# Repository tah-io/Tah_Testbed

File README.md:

Tah_Testbed
===========

Contains all the python and arduino test sketches for Tah Testbed

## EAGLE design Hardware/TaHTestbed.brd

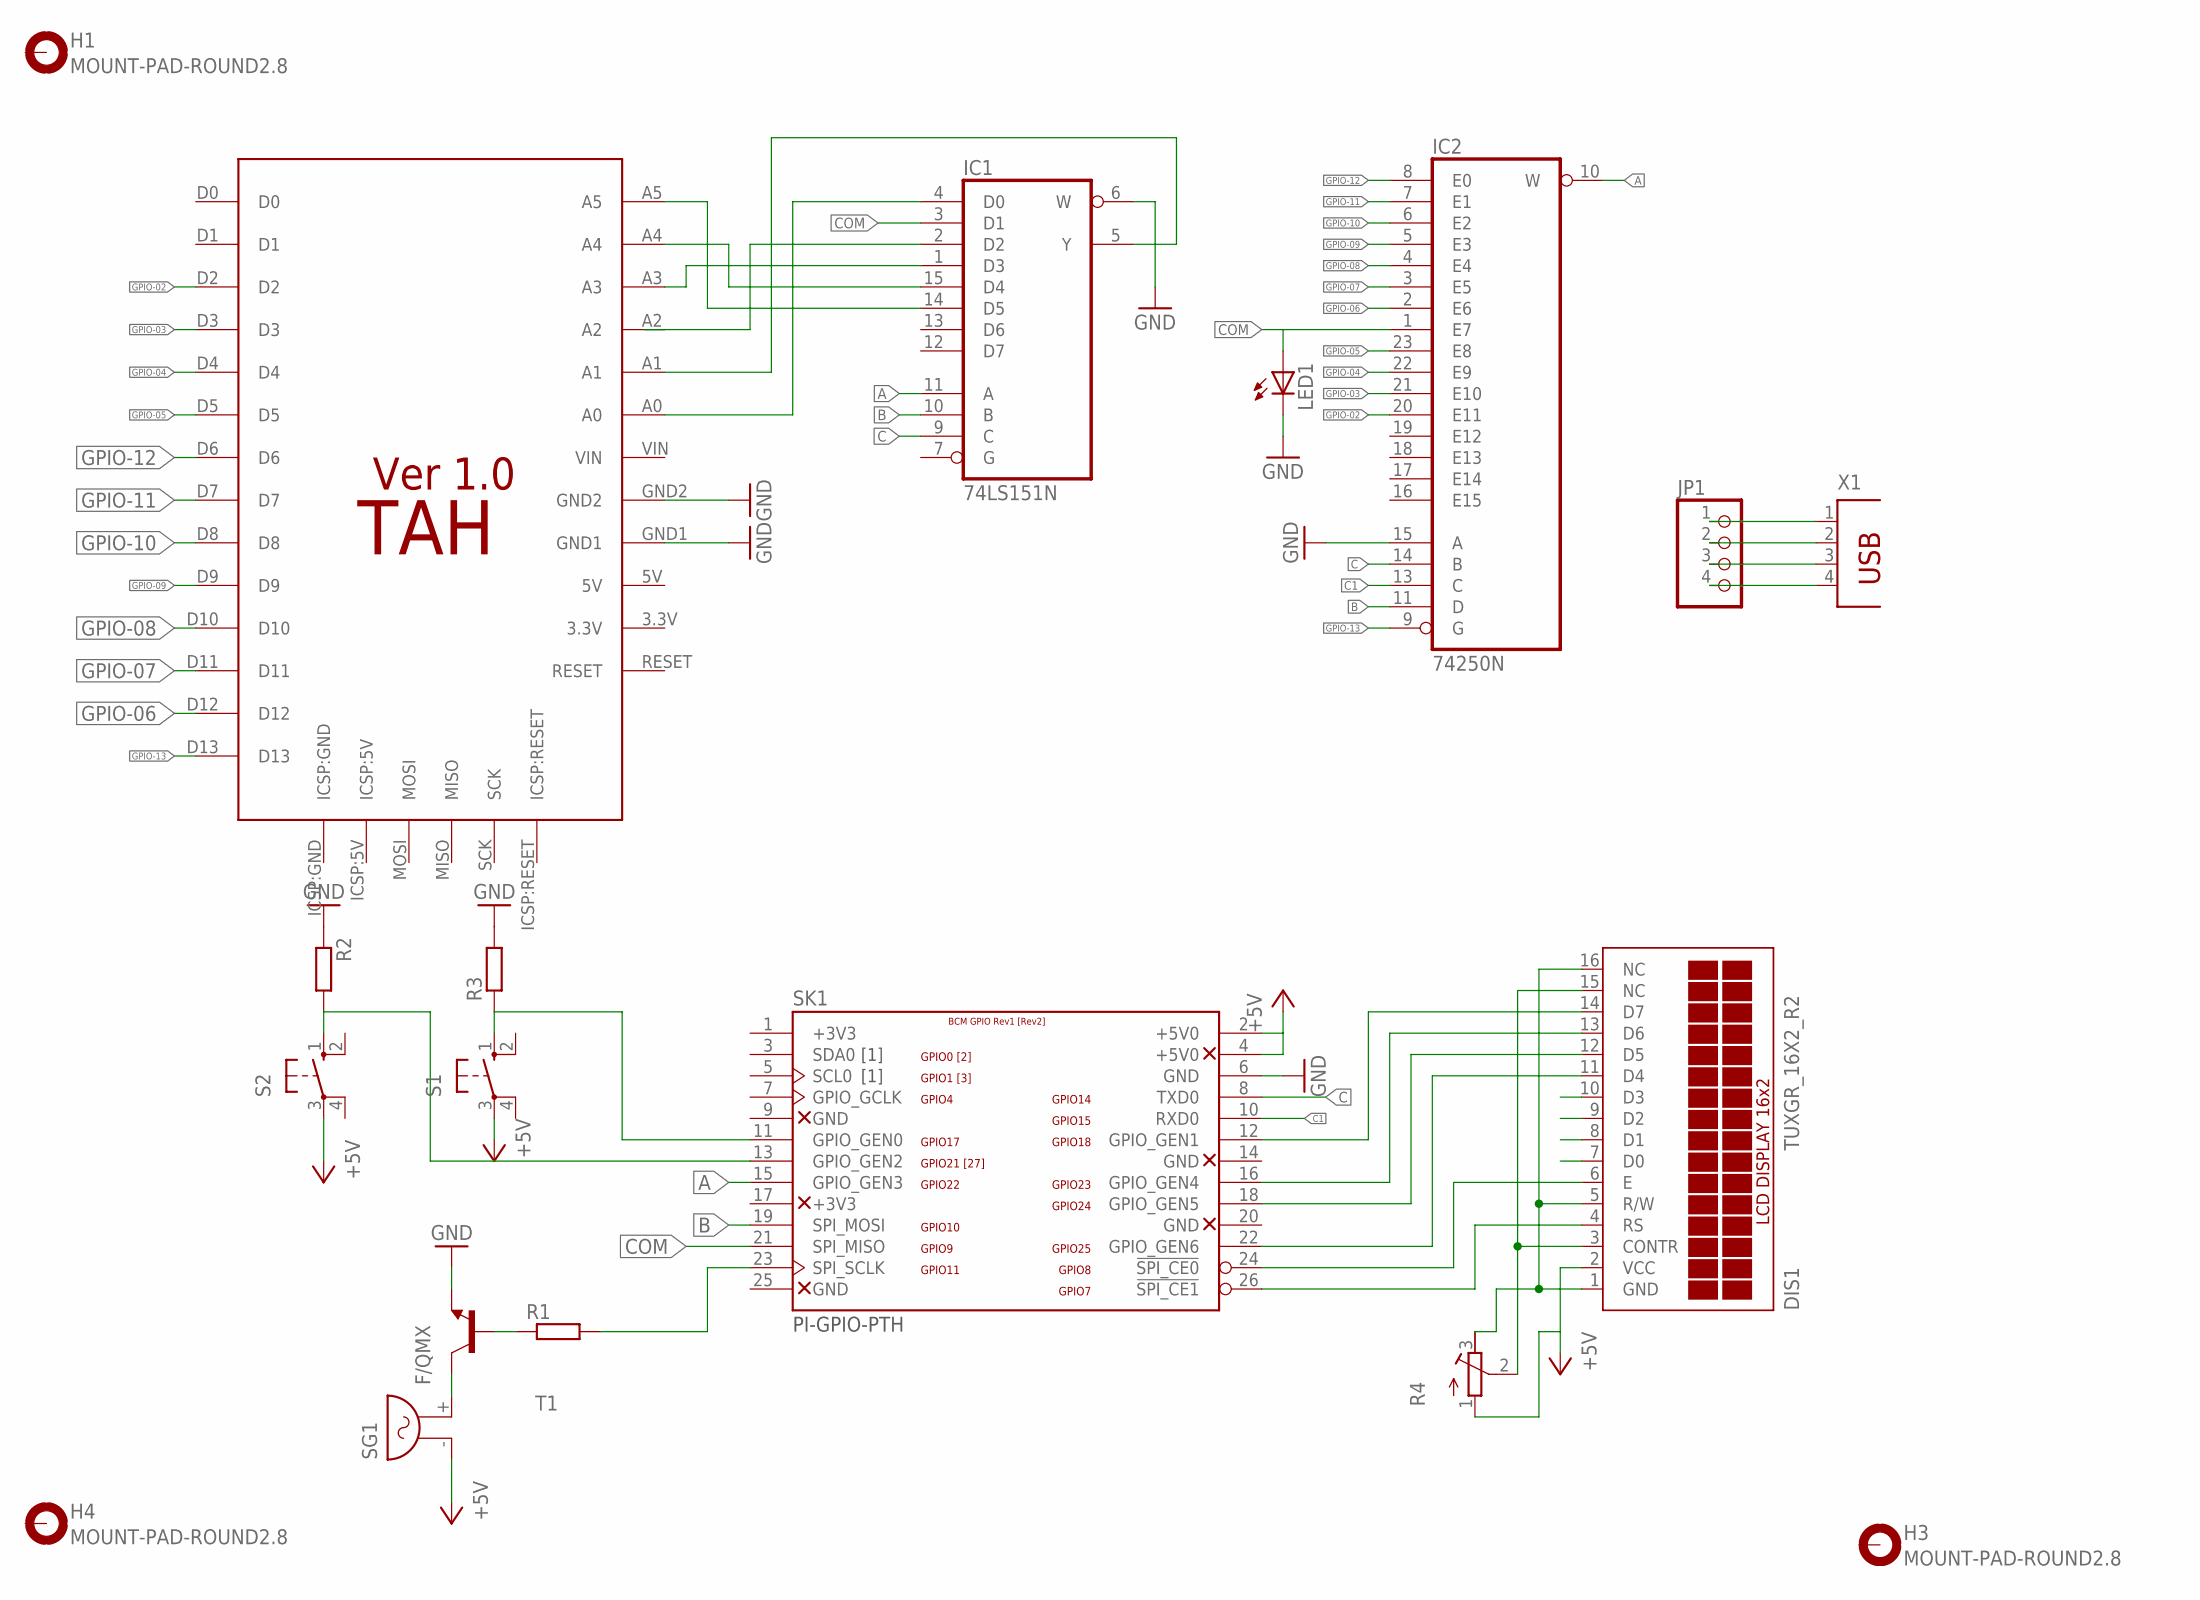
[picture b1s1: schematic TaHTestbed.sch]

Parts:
DIS1: TUXGR_16X2_R2
H1, H3, H4: MOUNT-PAD-ROUND2.8; 2,8-PAD
IC1: 74LS151N; DIL16
IC2: 74250N; DIL24-6
JP1: PINHD-1X4; 1X04
LED1: LEDCHIPLED_1206; CHIPLED_1206
R1: R-EU_0207/10; 0207/10
R2, R3: R-EU_0613/5V; P0613V
R4: R-TRIMM64Z; RTRIM64Z
S1, S2: 10-XX; B3F-10XX
SG1: F/QMX
SK1: PI-GPIO-PTH; GPIO-CONNECTOR
T1: BC547-NPN-TO92-CBE; TO92-CBE
U$2: TAH_FOOTPRINT_VER1.0; TAH_FOOTPRINT
X1: PN87520

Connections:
+3V3: SK1.1 (+3V3)
+5V: DIS1.2 (VCC), R4.1 (A), S1.3, S2.3, SG1.- (1), SK1.2 (+5V0), SK1.4 (+5V0)
A: IC1.11 (A), IC2.10 (W), SK1.15 (GPIO_GEN3)
B: IC1.10 (B), IC2.11 (D), SK1.19 (SPI_MOSI)
C: IC1.9 (C), IC2.14 (B), SK1.8 (TXD0)
C1: IC2.13 (C), SK1.10 (RXD0)
CM_IN: IC1.4 (D0), U$2.A0
COM: IC1.3 (D1), IC2.1 (E7), LED1.A, SK1.21 (SPI_MISO)
GND: IC1.6 (W), IC1.8 (GND), IC2.12 (GND), IC2.15 (A), LED1.C, R2.1, R3.2, SK1.6 (GND), T1.E, U$2.GND1, U$2.GND2
GPIO-02: IC2.20 (E11), U$2.D2
GPIO-03: IC2.21 (E10), U$2.D3
GPIO-04: IC2.22 (E9), U$2.D4
GPIO-05: IC2.23 (E8), U$2.D5
GPIO-06: IC2.2 (E6), U$2.D12
GPIO-07: IC2.3 (E5), U$2.D11
GPIO-08: IC2.4 (E4), U$2.D10
GPIO-09: IC2.5 (E3), U$2.D9
GPIO-10: IC2.6 (E2), U$2.D8
GPIO-11: IC2.7 (E1), U$2.D7
GPIO-12: IC2.8 (E0), U$2.D6
GPIO-13: IC2.9 (G), U$2.D13
unnamed: IC1.14 (D5), U$2.A5
unnamed: IC1.15 (D4), U$2.A4
unnamed: IC1.1 (D3), U$2.A3
unnamed: DIS1.4 (RS), SK1.26 (!SPI_CE1)
unnamed: IC1.2 (D2), U$2.A2
unnamed: DIS1.6 (E), SK1.24 (!SPI_CE0)
unnamed: DIS1.11 (D4), SK1.22 (GPIO_GEN6)
unnamed: DIS1.12 (D5), SK1.18 (GPIO_GEN5)
unnamed: DIS1.13 (D6), SK1.16 (GPIO_GEN4)
unnamed: DIS1.14 (D7), SK1.12 (GPIO_GEN1)
unnamed: JP1.1, X1.1
unnamed: IC1.5 (Y), U$2.A1
unnamed: DIS1.1 (GND), DIS1.5 (R/W), DIS1.16 (NC), R4.3 (E)
unnamed: R1.2, SK1.23 (SPI_SCLK)
unnamed: R1.1, T1.B
unnamed: DIS1.3 (CONTR), DIS1.15 (NC), R4.2 (S)
unnamed: SG1.+ (2), T1.C
unnamed: R3.1, S1.1 (S), SK1.11 (GPIO_GEN0)
unnamed: R2.2, S2.1 (S), SK1.13 (GPIO_GEN2)
unnamed: JP1.2, X1.2
unnamed: JP1.3, X1.3
unnamed: JP1.4, X1.4
VCC: IC1.16 (VCC), IC2.24 (VCC)

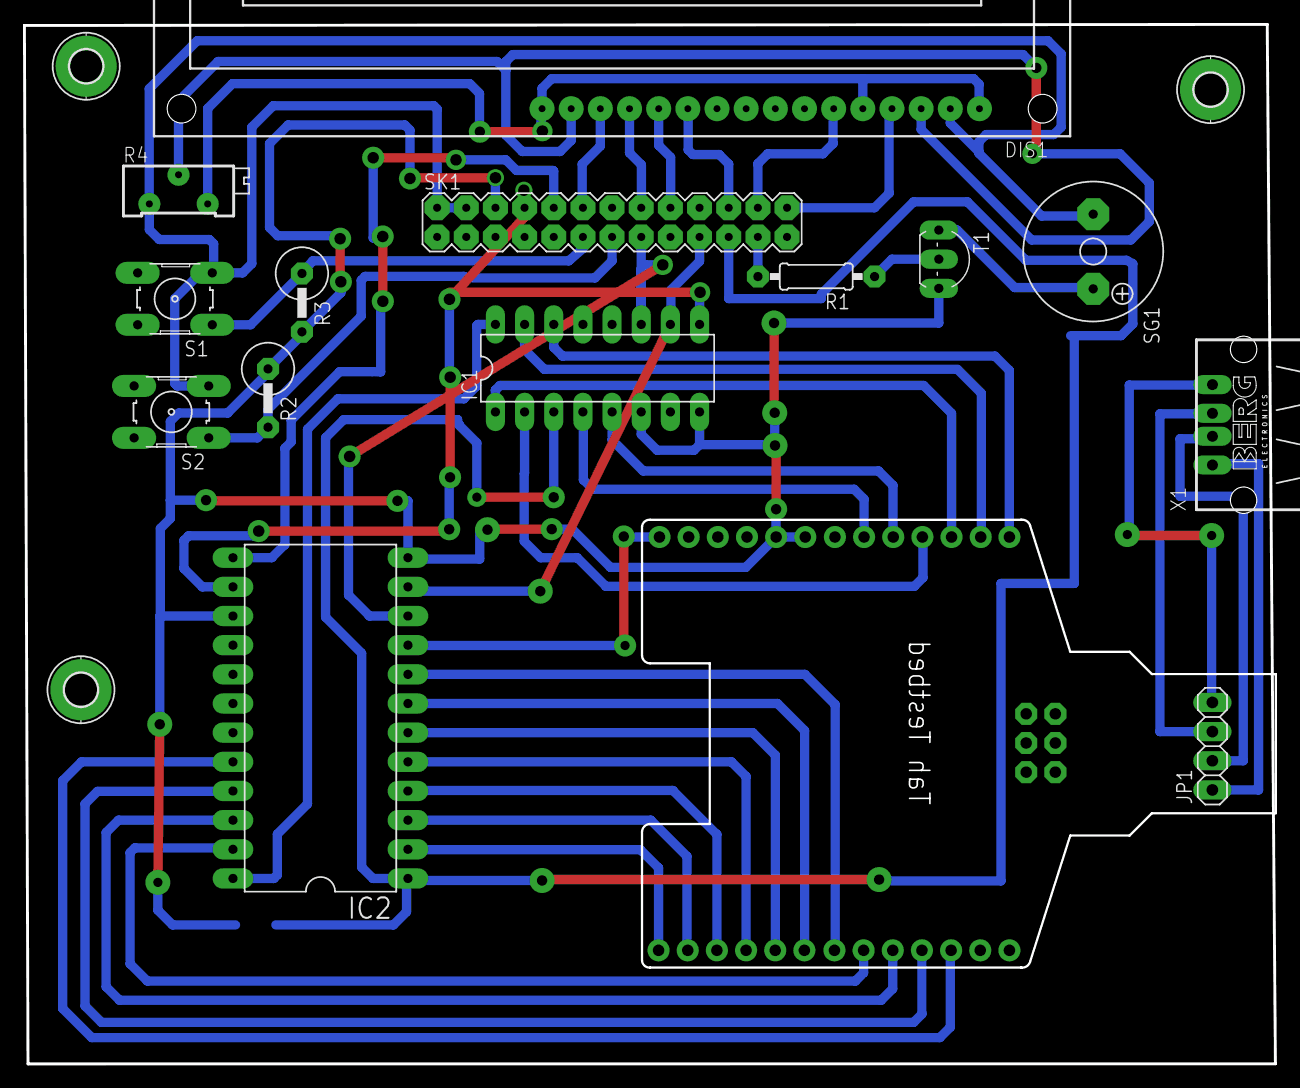
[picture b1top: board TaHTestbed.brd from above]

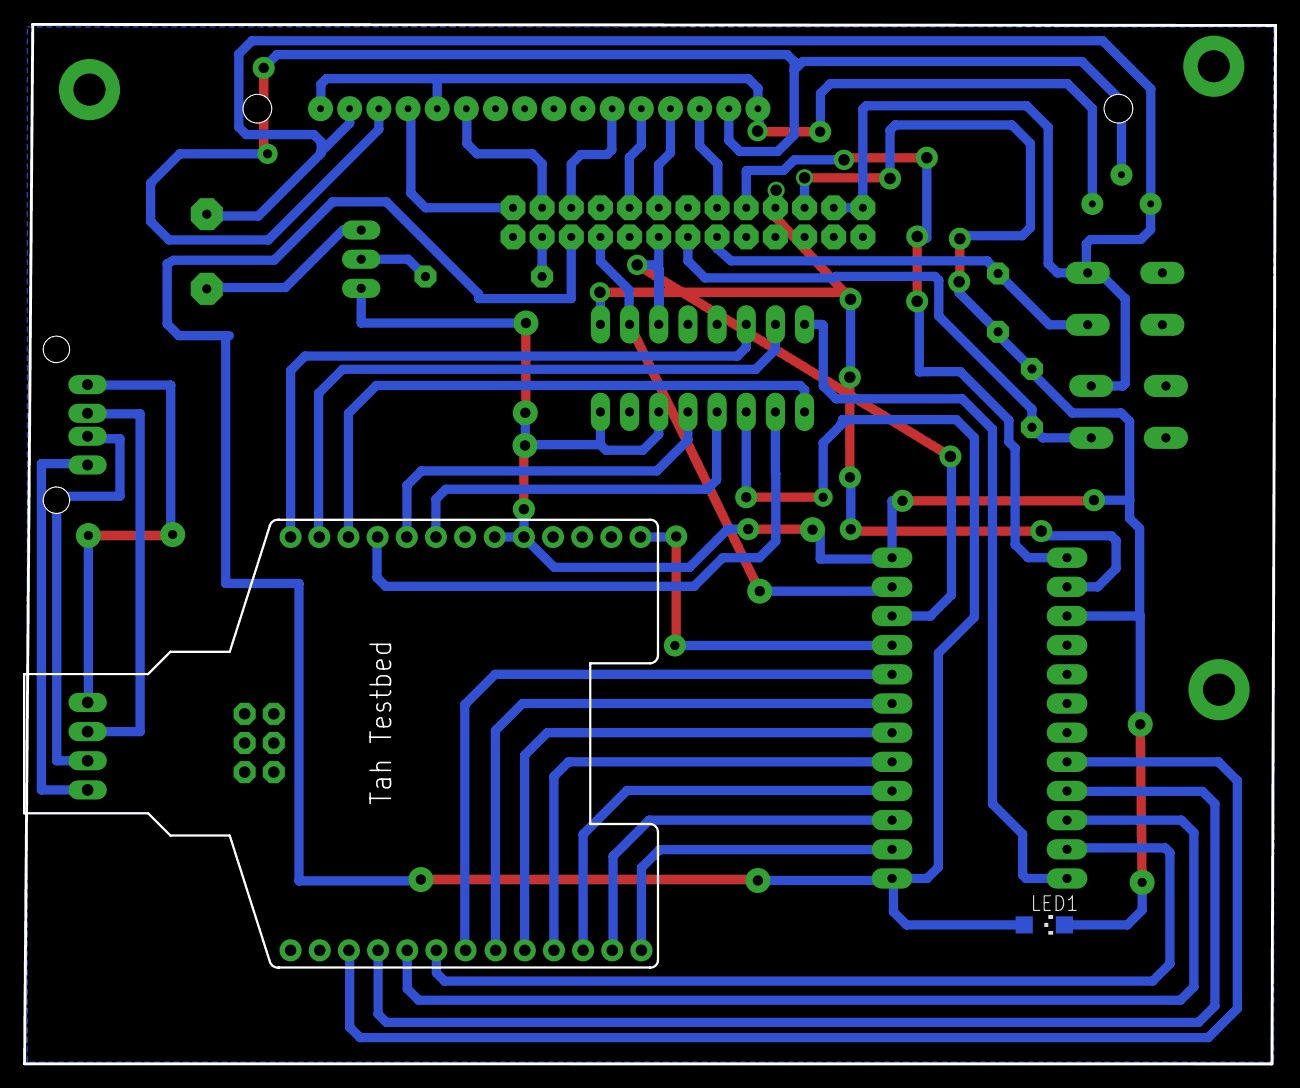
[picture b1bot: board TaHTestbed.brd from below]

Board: 2 copper layers, 109.0 x 90.5 mm, 19 parts (2 on the bottom side), 43 nets.

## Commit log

2014-11-12 Added Tah Testbed files
2014-11-26 Added Bootloader section
2014-11-27 Updated files
2014-11-29 new py script for testbed. merge conflict resoved.
2014-12-01 Updated Arduino Make file, Fixed make & make upload issue
2014-12-02 Updated mainTestbed.py
2014-12-02 Added Bootloader code to mainTestbed.py
2014-12-04 Added ArdSCL
2014-12-04 added Excel file
2014-12-06 Added csv to mainTestbed.py
2014-12-13 Added tested board
2015-01-12 Moved all logs to logs/
2015-01-12 Rename lcd_1 to lcd
2015-01-12 Remove obsolete files
2015-01-14 Changes to maintestbed.py
    Catch keyboard interrupt
    Push to logs/
    Datestamp for logs
2015-01-14 Fix datetime import
2015-01-14 Add statement after keyboardinterrupt
2015-01-14 Fix long durations with precompiled folders for different ports
2015-01-14 Fix build time issues
2015-02-16 Added schematic and board file for testbed
2015-02-22 Add license
